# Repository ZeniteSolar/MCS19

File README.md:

# MCS19
**M**ódulo de **C**arregamento do **S**istema 2019  
Embarcação Guarapuvu II  
Equipe Zênite Solar  

### Sobre

Este módulo é responsável por gerenciar o carregamento do sistema com a finalidade de garantir segurança para a embarcação.

#### Requisitos e Abordagens
1. Gerenciar a conexão elétrica entre as baterias e o restante do sistema.
    - Utilizar de um relé de alta potência.
    - Ser controlado através da rede CAN da embarcação.
2. Proteger o sistema de falhas por sobre-corrente.
    - Utilizar de um fusível corretamente dimensionado.
3. Realizar o carregamento do banco de capacitores de maneira segura.
    - Utilização de um circuito de inrush.
        - Utilizar de um NTC para limitar o di/dt.
        - Utilizar de um resistor para limitar o pico de corrente
        - Utilizar de um relé para garantir a desconexão completa entre o sistema
      e o banco de baterias.
4. Facilitar o diagnóstico
    - Utilizar reportagens pela rede CAN
    - Utilizar LEDs e Buzzer
        - Sinalizar o estado dos relés
            - Relé do inrush
            - Relé principal
        - Sinalizar o estado do fusível principal
5. Garantir fixação mecânica que não flexione a PCB
    - Utilizar estrutura auxiliar de material isolante

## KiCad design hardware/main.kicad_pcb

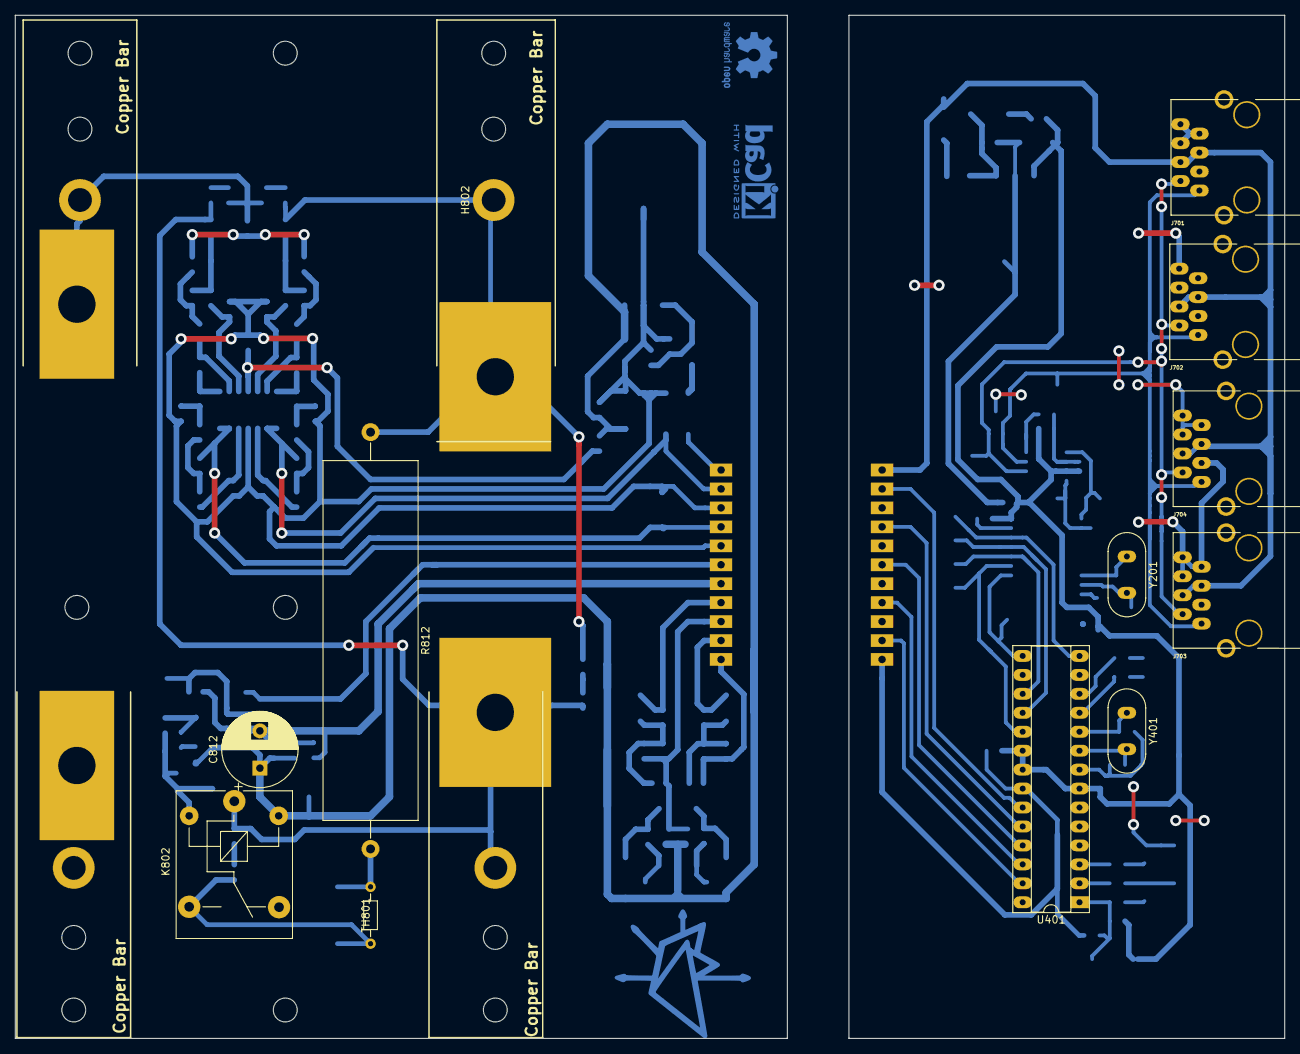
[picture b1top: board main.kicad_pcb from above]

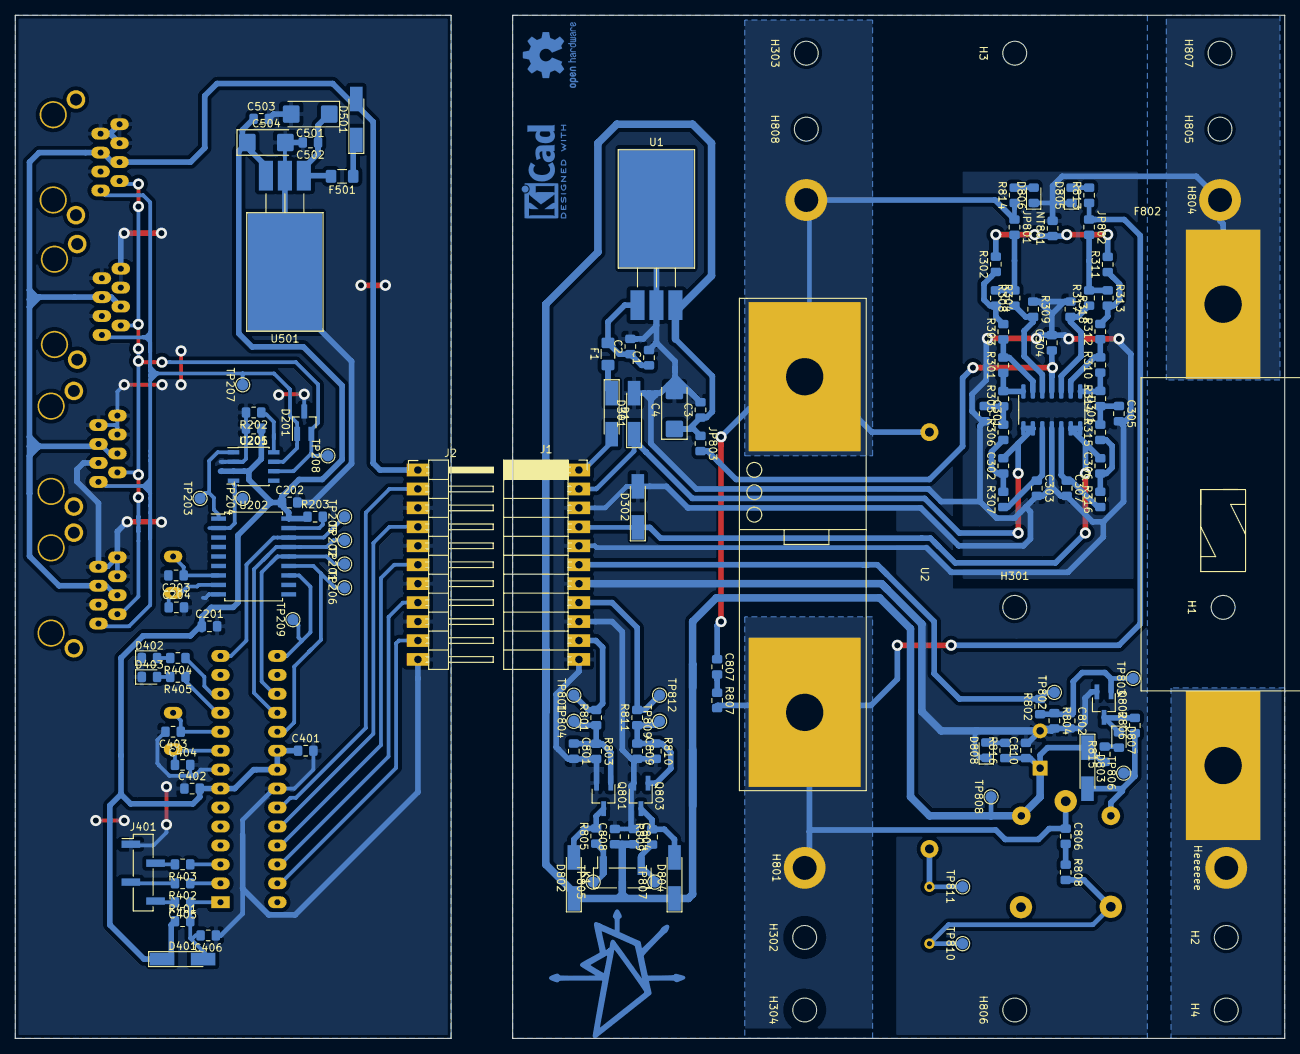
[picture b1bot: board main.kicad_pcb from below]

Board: 2 copper layers, 170.2 x 137.2 mm, 160 parts (147 on the bottom side), 83 nets.

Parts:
C1: 1uF; C_0805_2012Metric_Pad1.15x1.40mm_HandSolder
C2, C3, C201, C202, C205, C401, C402, C405, C406, C502, C503: 100nF; C_0805_2012Metric_Pad1.15x1.40mm_HandSolder
C4, C501, C504: 1uF; CP_EIA-6032-20_AVX-F_Pad2.25x2.35mm_HandSolder
C203, C204, C403, C404: 22pF; C_0805_2012Metric_Pad1.15x1.40mm_HandSolder
C301, C302, C303, C304, C305, C306, C307, C801, C802, C804, C806, C807, C808, C809, C810: 100n; C_0805_2012Metric_Pad1.15x1.40mm_HandSolder
C812: 4700u; CP_Radial_D10.0mm_P5.00mm
D1, D401, D501, D802, D803, D804: LL4148; D_MiniMELF_Handsoldering
D201: pesd1can; SOT-23_Handsoldering
D301, D302: 4V7; D_MiniMELF_Handsoldering
D402, D403: LED_RED; LED_0805_2012Metric_Pad1.15x1.40mm_HandSolder
D805: RED_LED; LED_0805_2012Metric_Pad1.15x1.40mm_HandSolder
D806, D808: GRN_LED; LED_0805_2012Metric_Pad1.15x1.40mm_HandSolder
D807: YLW_LED; LED_0805_2012Metric_Pad1.15x1.40mm_HandSolder
F1, F501: 500mA; Fuse_1206_3216Metric_Pad1.42x1.75mm_HandSolder
F802: Fuse Mega 200A; MegaFuse
H1, H2, H3, H4, H301, H302, H303, H304, H805, H806, H807, H808: MountingHole; MountingHole_3.2mm_M3
H801: U_BAT+; MountingHole_3.2mm_M3_DIN965_Pad
H802: +BAT; MountingHole_3.2mm_M3_DIN965_Pad
H804: F_BAT-; MountingHole_3.2mm_M3_DIN965_Pad
Heeeeee: U_BAT-; MountingHole_3.2mm_M3_DIN965_Pad
J1: Conn_01x11; PinSocket_1x11_P2.54mm_Horizontal
J2: Conn_01x11; PinHeader_1x11_P2.54mm_Horizontal
J401: USART; PinHeader_1x04_P2.54mm_Vertical_SMD_Pin1Left
J701, J702, J703, J704: 8P8C_Shielded; RJ45_YH59_01
JP801, JP802, JP803: Jp_TEST; R_0805_2012Metric_Pad1.15x1.40mm_HandSolder
K1: K100A; PinHeader_1x03_P2.54mm_Vertical_SMD_Pin1Right
K802: SANYOU_SRD_Form_C; Relay_SPDT_SANYOU_SRD_Series_Form_C
LOGO1: Logo_Open_Hardware_Small; zenite
LOGO2: Logo_Open_Hardware_Small; OSHW-Logo2_9.8x8mm_Copper
LOGO3: Logo_Open_Hardware_Small; KiCad-Logo2_5mm_Copper
NT801: Net-Tie_2; R_0805_2012Metric_Pad1.15x1.40mm_HandSolder
Q801, Q803: BCV27; TSOT-23_HandSoldering
Q802: Q_NPN_BEC; TSOT-23_HandSoldering
R202: 4k7; R_0805_2012Metric_Pad1.15x1.40mm_HandSolder
R203, R301, R303, R304, R308, R309, R310, R312, R313, R317, R318, R401, R803, R804, R810: 10k; R_0805_2012Metric_Pad1.15x1.40mm_HandSolder
R302, R311: 100k; R_0805_2012Metric_Pad1.15x1.40mm_HandSolder
R305, R306, R307, R314, R315, R316, R402, R403, R404, R405: 1k; R_0805_2012Metric_Pad1.15x1.40mm_HandSolder
R801, R802, R811: 1k2; R_0805_2012Metric_Pad1.15x1.40mm_HandSolder
R805, R806, R809: 120; R_0805_2012Metric_Pad1.15x1.40mm_HandSolder
R807, R808: 1R; R_0805_2012Metric_Pad1.15x1.40mm_HandSolder
R812: 10R; R_Axial_Power_L48.0mm_W12.5mm_P55.88mm
R813, R814: 2k5; R_0805_2012Metric_Pad1.15x1.40mm_HandSolder
R815, R816: 470; R_0805_2012Metric_Pad1.15x1.40mm_HandSolder
TH801: 60R; R_Axial_DIN0204_L3.6mm_D1.6mm_P7.62mm_Horizontal
TP201: SI; TestPoint_Pad_D1.5mm
TP202: SO; TestPoint_Pad_D1.5mm
TP203: TXCAN; TestPoint_Pad_D1.5mm
TP204: RXCAN; TestPoint_Pad_D1.5mm
TP205: SC; TestPoint_Pad_D1.5mm
TP206: SCK; TestPoint_Pad_D1.5mm
TP207: CAN_H; TestPoint_Pad_D1.5mm
TP208: CAN_L; TestPoint_Pad_D1.5mm
TP209: INT; TestPoint_Pad_D1.5mm
TP801: RL_ON; TestPoint_Pad_D1.5mm
TP802: Charge; TestPoint_Pad_D1.5mm
TP803: B_CH; TestPoint_Pad_D1.5mm
TP804: B_ON; TestPoint_Pad_D1.5mm
TP805: ON; TestPoint_Pad_D1.5mm
TP806: CH-; TestPoint_Pad_D1.5mm
TP807: OFF; TestPoint_Pad_D1.5mm
TP808: CH+; TestPoint_Pad_D1.5mm
TP809: B_OFF; TestPoint_Pad_D1.5mm
TP810: TH+; TestPoint_Pad_D1.5mm
TP811: TH-; TestPoint_Pad_D1.5mm
TP812: RL_OFF; TestPoint_Pad_D1.5mm
U1: LM7812; TO-220-3_Horizontal_TabDown_SMD
U2: K100B; Mega_Relay_K100_separated
U201: MCP2551-I/SN; SOIC-8_3.9x4.9mm_P1.27mm
U202: MCP2515-xSO; SOIC-18W_7.5x11.6mm_P1.27mm
U301: LM324; SOIC-14_3.9x8.7mm_P1.27mm
U401: ATMEGA328P-PU; DIP-28_W7.62mm_Socket
U501: LM7805; TO-220-3_Horizontal_TabDown_SMD
Y201, Y401: 16MHz; Crystal_HC49-U_Vertical

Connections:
+5V: C201.1, C202.1, C205.1, C401.1, C402.2, C503.1, C504.1, D401.1, R203.1, R401.1, U201.3, U202.18, U401.7, U401.20, U401.21, U501.3
+12VA: C304.1, JP803.2, U301.4
/CHARGER/+12V: C3.1, C4.1, C804.2, C808.1, C810.1, C812.1, D802.1, D803.1, D804.1, JP803.1, K1.2, K802.5, R815.1, R816.1, TP808.1, U1.3
/CHARGER/+18V_IN: D1.2, J1.1
/CHARGER/+CAP: C807.1, H802.1, JP801.1, R812.1, R814.1, U2.4
/CHARGER/CH: K802.3, R808.2, TH801.2......, TP810.1
/CHARGER/Charge: J1.6, R802.2, TP802.1
/CHARGER/RL_OFF: J1.8, R811.2, TP812.1
/CHARGER/RL_ON: J1.10, R801.2, TP801.1
/CHARGER/S_RL_ON: D807.1, Q802.3, R806.2
/CHARGER/U_BAT+: C806.1, H801.1, JP802.1, K802.1, R807.2, R813.1, U2.5
/CHARGER/U_BAT-: F802.2, Heeeeee.1
/CHARGER/sheet5CBAED96/in1+: JP801.2, R304.1, R308.2
/CHARGER/sheet5CBAED96/in2+: JP802.2, R313.1, R317.2
/CHARGER/sig_bat+: C306.2, D302.1, J1.4, U301.13, U301.14
/CHARGER/sig_cap+: C302.2, D301.1, J1.2, U301.8, U301.9
/CONTROLLER/+18V_OUT: D501.2, J2.1, J701.4, J701.5, J702.4, J702.5, J703.4, J703.5, J704.4, J704.5
/CONTROLLER/Charge: J2.6, U401.25
/CONTROLLER/MISO: TP202.1, U202.15, U401.18
/CONTROLLER/MOSI: TP201.1, U202.14, U401.17
/CONTROLLER/RL_OFF: J2.8, U401.26
/CONTROLLER/RL_ON: J2.10, U401.27
/CONTROLLER/SCK: TP206.1, U202.13, U401.19
/CONTROLLER/sheet5CA5A59C/CAN_H: D201.1, J701.1, J702.1, J703.1, J704.1, TP207.1, U201.7
/CONTROLLER/sheet5CA5A59C/CAN_L: D201.2, J701.2, J702.2, J703.2, J704.2, TP208.1, U201.6
/CONTROLLER/sheet5CA5A59C/CS: TP205.1, U202.16, U401.14
/CONTROLLER/sheet5CA5A59C/INT: TP209.1, U202.12, U401.15
/CONTROLLER/sheet5CA5A59C/RXCAN: TP204.1, U201.4, U202.2
/CONTROLLER/sheet5CA5A59C/TXCAN: TP203.1, U201.1, U202.1
/CONTROLLER/sheet5CA5A59D/LED1: R405.1, U401.11
/CONTROLLER/sheet5CA5A59D/LED2: R404.1, U401.12
/CONTROLLER/sheet5CA5A59D/RESET: C405.1, C406.2, D401.2, R401.2, U401.1
/CONTROLLER/sheet5CA5A59D/USART_RX: R402.1, U401.2
/CONTROLLER/sheet5CA5A59D/USART_TX: R403.1, U401.3
/CONTROLLER/sig_bat+: J2.4, U401.24
/CONTROLLER/sig_cap+: J2.2, U401.23
GND: C201.2, C202.2, C203.2, C204.2, C205.2, C401.2, C402.1, C403.2, C404.2, C406.1, C501.2, C502.2, C503.2, C504.2, D201.3, D402.1, D403.1, J2.3, J2.5, J2.7, J2.9, J2.11, J401.1, J701.3, J701.6, J701.7, J701.8, J702.3, J702.6, J702.7, J702.8, J703.3, J703.6, J703.7, J703.8, J704.3, J704.6, J704.7, J704.8, R202.2, U201.2, U202.9, U401.8, U401.22, U501.2
GNDA: NT801.1, R302.2, R311.2
GNDPWR: C1.2, C2.2, C3.2, C4.2, C301.2, C303.2, C304.2, C305.2, C307.2, C801.2, C802.2, C804.1, C808.2, C809.2, C810.2, C812.2, D301.2, D302.2, D805.1, D806.1, D808.1, F802.1, H804.1, J1.3, J1.5, J1.7, J1.9, J1.11, NT801.2, Q801.2, Q802.2, Q803.2, R309.1, R318.1, R803.2, R804.2, R810.2, U1.2, U301.11
unnamed: C1.1, C2.1, F1.2, U1.1
unnamed: C203.1, U202.7, Y201.1
unnamed: C204.1, U202.8, Y201.2
unnamed: C301.1, R305.1, R306.2
unnamed: C302.1, R306.1, R307.2
unnamed: C303.1, R307.1, U301.10
unnamed: C305.1, R314.1, R315.2
unnamed: C306.1, R315.1, R316.2
unnamed: C307.1, R316.1, U301.12
unnamed: C403.1, U401.10, Y401.1
unnamed: C404.1, U401.9, Y401.2
unnamed: C405.2, J401.4
unnamed: C501.1, C502.1, F501.2, U501.1
unnamed: C801.1, Q801.1, R801.1, R803.1, TP804.1
unnamed: C802.1, Q802.1, R802.1, R804.1, TP803.1
unnamed: C806.2, R808.1
unnamed: C807.2, R807.1
unnamed: C809.1, Q803.1, R810.1, R811.1, TP809.1
unnamed: D1.1, F1.1
unnamed: D402.2, R404.2
unnamed: D403.2, R405.2
unnamed: D501.1, F501.1
unnamed: D802.2, Q801.3, R805.2
unnamed: D803.2, K802.2, R806.1, TP806.1
unnamed: D804.2, Q803.3, R809.2
unnamed: D805.2, R813.2
unnamed: D806.2, R814.2
unnamed: D807.2, R815.2
unnamed: D808.2, R816.2
unnamed: J401.2, R403.2
unnamed: J401.3, R402.2
unnamed: K1.1, R805.1, TP805.1
unnamed: K1.3, R809.1, TP807.1
unnamed: R202.1, U201.8
unnamed: R203.2, U202.17
unnamed: R301.1, R305.2, U301.7
unnamed: R301.2, R303.1, U301.6
unnamed: R302.1, R303.2, R304.2
unnamed: R308.1, R309.2, U301.5
unnamed: R310.1, R314.2, U301.1
unnamed: R310.2, R312.1, U301.2
unnamed: R311.1, R312.2, R313.2
unnamed: R317.1, R318.2, U301.3
unnamed: R812.2, TH801.1, TP811.1

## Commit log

2019-03-23 Informações básicas adicionadas
2019-03-23 Ignore LTSPCIE data
2019-03-23 initial simulations
2019-03-23 Descrição das simulações adicionada
2019-03-28 NÃO FINALIZADA Primeira versão do esquematico Foi reciclado o modulo atmega e can do MSC19
2019-03-29 Primeira versão do esquematico finalizada Falta DRC
2019-03-31 O fusivel do sistema foi movido pro GND
2019-03-31 Abstração do esquemático modificada para separar as duas placas e mostrar a conexão entre elas na folha principal
2019-03-31 TO-DO List criada na folha principal
2019-03-31 Alimentação de 12V criada no Charger, que recebe 18V do Controller
2019-03-31 Folha modificada para A3
2019-03-31 CAN CTRL_D / CAN_ON_OFF removidos.
2019-03-31 Novos capacitores anotados
2019-03-31 Analog passado para o Charger
2019-04-02 Esquematico primeira versão Erro de referencia dos componentes na PCB com os do Esquematico solucionados
    Pontos de teste adicionados
    Alimentar o analog com +12V
    Adicionar Snubber para os reles
2019-04-02 Footprints
2019-04-02 Generic layout and relay driver
2019-04-04 Copper bar fixation
2019-04-04 Layout and Relay footprint
2019-04-05 Ampop layout not finished
2019-04-06 Circuito ampop incompleto
2019-04-14 Layout retrabalhado. Não finalizado.
2019-04-15 Signals tracks routed
2019-04-15 First version PCB
2019-04-19 Small updates
2019-04-21 Connector to join the modules, were centrailized Compacted Atmega PCB
2019-04-21 Files organization
2019-04-21 3D fixation
2019-04-21 small update
2019-04-23 export files
2019-05-03 Ampop gain error
2019-05-16 Imported MSC19 code and MCS17 and merged
2019-05-16 Charging logic finalized
    time and voltage verification before turn boat on ,when is charging
    if is under-voltage enter in error state
2019-05-18 Under_voltage error after charge fixed
    Quando testava se depois de carregar o capacitor, ele estava carregado, o modulo comparava entre uma constante e a tensão do capacitor.
    Essa logica tinha um erro quando a tensão da bateria era menor que a
    maxima, pois o capacitor nunca chegava na constante.
    Para solucionar isso o codigo compara se a tensão do capacitor esta uma percentagem definida abaixo da bateria
2019-05-18 Declared functions and variables for the wait for reset tasK
2019-05-19 no work :(
2019-05-19 small error
2019-05-20 Is not working
2019-05-20 waiting for reset task working!!!
    In function machine_run, in switch of state_machine was missing a
    "break" in case STATE_WAITING_RESET
    In the end of error_task function was calling the set_state_initializing
    function ignoring all states called before that,then set_state_initializing was moved to
    the begining of error task function.
2019-08-05 realy state no can
2020-01-19 reorganized, 3d exported
2020-01-20 avr-can-lib updated
2020-01-20 can_ids removed, makelibs updated
2020-01-20 makelibs updated
2020-01-20 updating MAB CAN messages
2020-01-20 updating MIC CAN messages
2020-01-20 updating MCS CAN messages
2020-01-21 updating MAM and GENERIC CAN messages
2020-01-21 cleaned
2020-01-21 compiling but need to be tested
2020-07-13 export 3D and layout images
2022-03-19 Add firmware gitignore.
2022-03-19 Remove binaries
2022-03-19 makefile: Add several compiler flags, change optimization to 's', use system installed avr-gcc.
2022-03-19 Use extern modifier to fix duplicated variables being defined on newer GCC
2022-03-19 can_app: Fix switch fall through.
2022-03-19 Fix missing declarations.
2022-07-01 temporary commit
2022-11-08 fix can_app frequencies
2025-05-31 standard update
2025-05-31 change adc logic to circular buffer
2025-05-31 main does not touch LED
2025-05-31 Better macros, using new adc logic
2025-05-31 using new adc logic - NO max min implementation yet
2025-05-31 new macros
2025-05-31 Linearized adc channels
2025-05-31 minor changes
2025-05-31 Hear usart after deploying code
2025-05-31 linearization files
2025-05-31 copy gitignore from MSR22
2025-06-03 WARNING for non-integer cap_app clk_div frequencies
2025-06-11 standard code - comment relay_test_mode
